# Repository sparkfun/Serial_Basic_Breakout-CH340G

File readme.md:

SparkFun Serial Basic Breakout - CH340G
========================================

[*SparkFun Serial Basic Breakout - CH340G (DEV-14050)*](https://www.sparkfun.com/products/14050)

This is a CH340G based board that converts USB to Serial. 
It follows the standard Arduino pin out so this can be used to program the Pro and Pro Mini line of Arduinos. 
It can also be used as a general serial device for debugging (such as with a GPS module).

Board is default 3.3V output and 3.3V serial signals but cutting the trace on the back of the board and 
soldering a jumper to 5V changes the VCC pin to output 5V and changes serial comm signals to 5V.

Repository Contents
-------------------

* **/Hardware** - Eagle design files (.brd, .sch)
* **/Production** - Production panel files (.brd)

Documentation
--------------
* **[Hookup Guide](https://learn.sparkfun.com/tutorials/serial-basic-hookup-guide)** - Basic hookup guide
* **[How to Install CH340 Drivers](https://www.sparkfun.com/ch340)** - Drivers if you need
* **[SparkFun Fritzing repo](https://github.com/sparkfun/Fritzing_Parts/blob/main/products/14050_sfe_serial_basic_breakout_ch340g.fzpz)** - Fritzing diagrams for SparkFun products.
* **[SparkFun 3D Model repo](https://github.com/sparkfun/3D_Models)** - 3D models of SparkFun products. 
* **[SparkFun Graphical Datasheets](https://github.com/sparkfun/Graphical_Datasheets)** -Graphical Datasheets for various SparkFun products.

License Information
-------------------

This product is _**open source**_! 

Please review the LICENSE.md file for license information. 

If you have any questions or concerns on licensing, please contact techsupport@sparkfun.com.

Distributed as-is; no warranty is given.

- Your friends at SparkFun.

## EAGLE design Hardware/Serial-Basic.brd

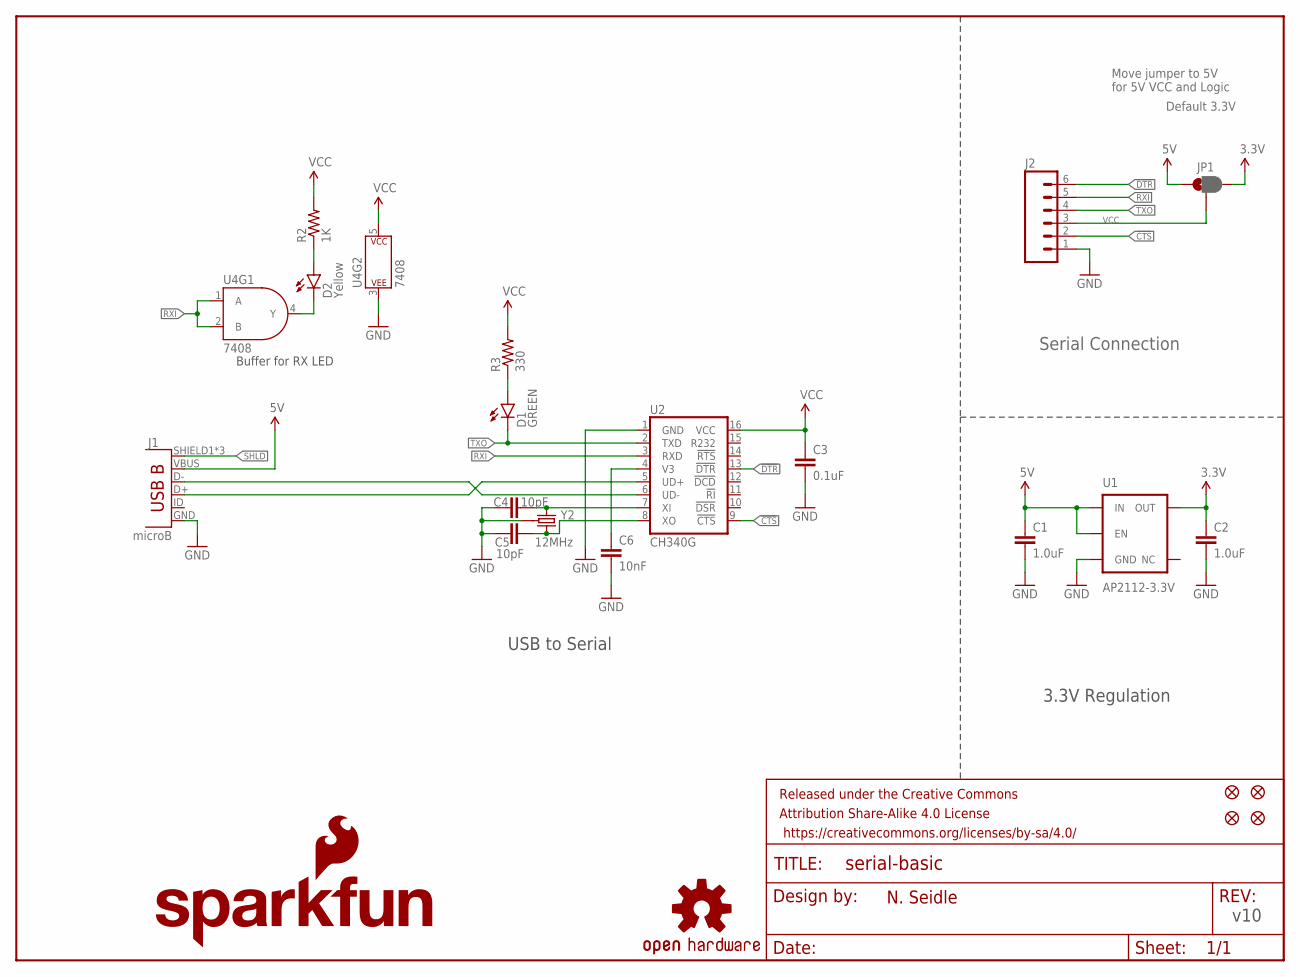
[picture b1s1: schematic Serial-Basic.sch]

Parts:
C1, C2: 1.0uF; 0603-CAP
C3: 0.1uF; 0603-CAP
C4, C5: 10pF; 0603-CAP
C6: 10nF; 0603-CAP
D1: GREEN; LED-0603
D2: Yellow; LED-0603
FRAME1: FRAME-LETTER; CREATIVE_COMMONS
J1: microB; USB-B-MICRO-SMD_V03
J2: M06SMD-FEMALE-V2; 1X06-SMD-FEMALE-V2
JP1: JUMPER-PAD-3-2OF3_NC_BY_PASTE; PAD-JUMPER-3-2OF3_NC_BY_PASTE_YES_SILK_FULL_BOX
JP3, JP4, JP5, JP6: FIDUCIAL1X2; FIDUCIAL-1X2
LOGO1: OSHW-LOGOS; OSHW-LOGO-S
LOGO2: SFE_LOGO_FLAME.1_INCH; SFE_LOGO_FLAME_.1
LOGO3: SFE_LOGO_NAME.1_INCH; SFE_LOGO_NAME_.1
R2: 1K; 0603-RES
R3: 330; 0603-RES
U1: AP2112-3.3V; SOT23-5
U2: CH340G; SO016
U4: 7408; SOT353
Y2: 12MHz; CRYSTAL-SMD-3.2X2.5

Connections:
3.3V: C2.1, JP1.3, U1.5 (OUT)
5V: C1.1, J1.VBUS, JP1.1, U1.1 (IN), U1.3 (EN)
!CTS: J2.2, U2.9 (!CTS)
!DTR: J2.6, U2.13 (!DTR)
GND: C1.2, C2.2, C3.2, C4.1, C5.1, C6.2, J1.GND, J2.1, U1.2 (GND), U2.1 (GND), U4.3 (P$V-), Y2.2 (GND), Y2.4 (GND)
unnamed: D1.A, R3.1
unnamed: D2.A, R2.1
unnamed: C5.2, U2.8 (XO), Y2.3 (2)
unnamed: C4.2, U2.7 (XI), Y2.1
unnamed: D2.C, U4.4 (Y)
unnamed: J1.D-, U2.6 (UD-)
unnamed: J1.D+, U2.5 (UD+)
RXI: J2.5, U2.3 (RXD), U4.1 (A), U4.2 (B)
SHLD: J1.SHIELD1 (SHIELD), J1.SHIELD2 (SHIELD), J1.SHIELD3 (SHIELD)
TXO: D1.C, J2.4, U2.2 (TXD)
V3: C6.1, U2.4 (V3)
VCC: C3.1, J2.3, JP1.2, R2.2, R3.2, U2.16 (VCC), U4.5 (P$V+)

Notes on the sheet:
Default 3.3V
v10
USB to Serial
3.3V Regulation
N. Seidle
Move jumper to 5V for 5V VCC and Logic
Buffer for RX LED
Serial Connection

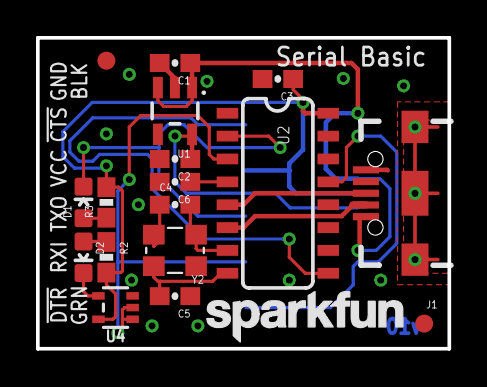
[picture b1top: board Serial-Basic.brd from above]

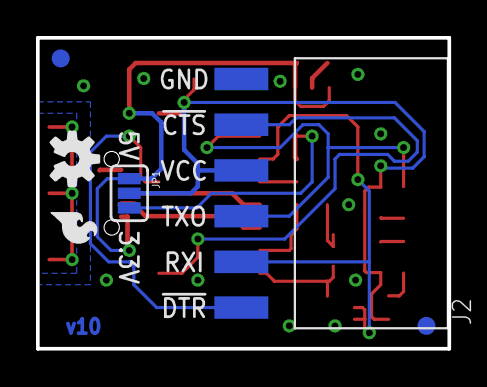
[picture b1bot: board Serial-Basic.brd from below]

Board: 2 copper layers, 22.9 x 17.3 mm, 25 parts (6 on the bottom side), 17 nets.

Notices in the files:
parts and their libraries:
SparkFun-Aesthetics: Licensing: CC v3.0 Share-Alike You are welcome to use this library for commercial purposes.
SparkFun-Aesthetics: Released under the Creative Commons Attribution Share-Alike 4.0 License
SparkFun-Aesthetics: https://creativecommons.org/licenses/by-sa/4.0
